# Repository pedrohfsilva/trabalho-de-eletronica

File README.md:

# Fonte de Tensão ajustável(3v - 12v)

Buscamos diagramar e construir uma fonte com capacidade para até 100mA de corrente e uma tensão ajustável dada uma fonte inicial de 127V.

## Transformador

O Transformador é necessário para ajustar a tensão alternada residencial com tensão maxima de 179.6V e frequência de 60Hz para uma tensão que o aparelho possa receber.

A tensão eficaz é o equivalente contínuo de uma fonte alternada e seu cálculo é dado por:  

$V{ef}=\frac{V{max}}{\sqrt{2}}$

$V{ef}=\frac{179.6}{\sqrt{2}}$

$V{ef}\approx127$

A razão entre o número de voltas na espira primária e secundária é diretamente proporcional a razão entre a voltagem primária e secundária 

Logo, a equação se dá por:

$\frac{V_1}{V_2}=\frac{N_1}{N_2}$

Aplicando:

$\frac{179.6}{24.6}=\frac{N_1}{N_2}$

## Diodos / Ponte de diodos

Sem diodos e com uma transformador $\frac{N_1}{N_2}=10$, a tensao em uma resistência, varia conforme o seguinte gráfico (apresentando tensões negativas, o que não é desejado)

Com uma retificador de meia onda, ou seja, apenas um diodo, a tensão em uma resistencia varia da seguinte maneira

Assim, será necessária uma ponte de diodos para retificar a corrente (manter o sentido da corrente após o transformador)
Um diodo permite que a corrente passe em apenas um sentido. Uma ponte de diodos associa 4 diodos como mostrado na imagem para que a fonte alternada de tensões positivas e negativas se polarize apenas em tensões positivas.

(note que dois diodos consomem cerca de 1.4v)

Cada diodo de sílicio consome cerca de 0.7V, e como são utilizados dois por vez, um consumo de 1.4V deve ser considerado. 

## Capacitor

Apos retificar a tensão, é necessário evitar que ela chegue a 0. Para isso, utilizaremos um capacitor, que impede a queda de tensão total, mantendo-a mais próxima de uma voltagem constante para a resistência final.

Em eletrônica, capacitância é uma grandeza oposta à voltagem, sendo gerada pelo acúmulo de carga em uma determinada região, sendo que há inexistência de corrente entre uma região e outra. 
Dessa forma, capacitores são dispositivos compostos por duas placas isoladas entre si e próximas, assim ao passar uma corrente por ele (a corrente não passa realmente pela existência de material isolante entre as placas, apenas é gerada pela indução das cargas), um dos lados terá acúmulo de elétrons que gerará uma indução crescente até que as placas atinjam seu limite de carga (no infinito). Quando a tensão da fonte for menor do que a sua interna, a carga acumulada gerará uma corrente no sentido inverso, até que ela seja novamente 0 (o que não chega a acontecer no nosso circuito).
O tempo de carga de um capacitor até que esse chegue a 98%, pode ser aproximado por $t=5\cdot R\cdot C$

Esse agora é o comportamento da tensão, com um capacitor em paralelo no circuito, a tensão ainda varia nesse padrão que se denomina ripple. E o valor do ripple(diferença entre máximo e mínimo) é calculado por ripple = $\frac{V_2-2\cdot D}{2\cdot f\cdot C\cdot R}$

O valor máximo é a tensão após a fonte de diodos, que é 24.6(medido no transformador)-2Diodos, = 23.2V
O valor mínimo é o maximo decrescido do ripple(cerca de 23.6V, considerando um ripple de 4.3%).

Considerando um ripple de 4.3% após a ponte de diodos (equivalente a 1V) e aplicando na fórmula, a capcitância encontrada é de 1mF, que é um valor comercial.
Agora, resta eliminar o ripple.

## Diodo zener

O diodo zener é um componente eletrônico que permite a passagem da corrente em apenas um sentido como um diodo normal, no outro sentido ele consome uma tensão cosntante. Ele é utilizado na fonte como um regulador de tensão, com o objetivo de manter uma corrente contínua. Para este projeto, a sua tensão limite é de 13V, pois, se esse limite não for atingido, ele não se torna condutor e 13V é o valor comercial mais próximo acima de 12,7V(valor do transitor mais o valor máximo fornecido). Além disso, ele opera a uma potência de 500 miliwatts.

## Transistor

O transistor bipolar é um componente que funciona como amplificador de corrente, sendo que a corrente do coletor para a base é cerca de 100 vezes menor do que a corrente da base para o emissor.
Utilizaremos ele para permitir a passagem da corrente estabilizada ao mesmo tempo em que recebe a tensão controlada pelo zener. O transistor consome 0.7V.

## Potenciometro

O potenciometro opera como uma resistência variável para permitir a troca de tensão fornecida. Quando o seu valor é mínimo, a tensão fornecida é a mesma da tensão que o zener permite menos a tensão consumida pelo transistor. Quando a resistência é máxima, a potência entregue é 0V. Para corrigir isso, adicionamos duas resistências de 820 em série após o potênciometro para que a voltagem mínima seja de cerca de 1.2V.
Foi utilizado um potênciometro de 10k.

# Tabela de Preços

|Componente|Preço unitário|Quantidade|Subtotal
|---|---|---|---|
[Led 5mm Verde](https://www.baudaeletronica.com.br/produto/led-difuso-5mm-verde)|R$ 0,27|1|R$ 0,27
[LED Difuso 3mm Vermelho](https://www.baudaeletronica.com.br/produto/led-difuso-3mm-vermelho)|R$ 0,25|3|R$ 0,75
[LED Difuso 5mm Azul](https://www.baudaeletronica.com.br/produto/led-difuso-5mm-azul)|R$ 0,27|1|R$ 0,27
[Resistor 820R 5% (2W)](https://www.baudaeletronica.com.br/produto/resistor-820r-5-2w.html)|R$ 0,42|4|R$ 1,68
[Transistor NPN 2N2222](https://www.baudaeletronica.com.br/produto/transistor-npn-2n2222.html)|R$ 0,55|4|R$ 2,20
[Ponte Retificadora KBPC1010](https://www.baudaeletronica.com.br/produto/ponte-retificadora-kbpc1010.html)|R$ 4,90|2|R$ 9,80
[Capacitor Eletrolítico 1000uF / 25V](https://www.baudaeletronica.com.br/produto/capacitor-eletrolitico-1000uf-25v-105c.html)|R$ 0,95|4|R$ 3,80
[Resistor 82R 5% (2W)](https://www.baudaeletronica.com.br/produto/resistor-82r-5-2w.html)|R$ 0,42|3|R$ 1,26
[Potenciômetro Linear de 10K (10000Ω)](https://www.baudaeletronica.com.br/produto/potenciometro-linear-de-10k-10000.html)|R$ 2,70|1|R$ 2,70
[Diodo Zener BZX55C (13V / 0.5W)](https://www.baudaeletronica.com.br/produto/diodo-zener-bzx55c-13v-05w.html)|R$ 0,09|5|R$ 0,45
[Resistor 5K1 5% (2W)](https://www.baudaeletronica.com.br/produto/resistor-5k1-5-2w.html)|R$ 0,42|3|R$ 1,26
[Protoboard 170 Pontos Azul](https://www.baudaeletronica.com.br/produto/protoboard-170-pontos-azul.html)|R$ 4,75|2|R$ 9,50
[Resistor 3K 5% (1/4W)](https://www.baudaeletronica.com.br/produto/resistor-3k-5-14w.html)|R$ 0,06|4|R$ 0,24
Frete|||R$ 18,16
TOTAL:|||R$ 52,34

# Circuito do Falstad

## Link para o circuito
[https://tinyurl.com/24aza57k](https://tinyurl.com/2dmqjkqc)

# Esquemático da PCB (EAGLE)

# PCB (EAGLE)

# Imagens - Projeto

# Vídeo - Projeto
https://youtu.be/xrW4_Q9_DJc

## Alunos

Bruno Figueiredo Lima - 14562383

Gabriel Antunes Afonso de Araujo - 14571077

Lázaro Pereira Vinaud Neto - 14675396

Pedro Henrique Ferreira Silva - 14677526

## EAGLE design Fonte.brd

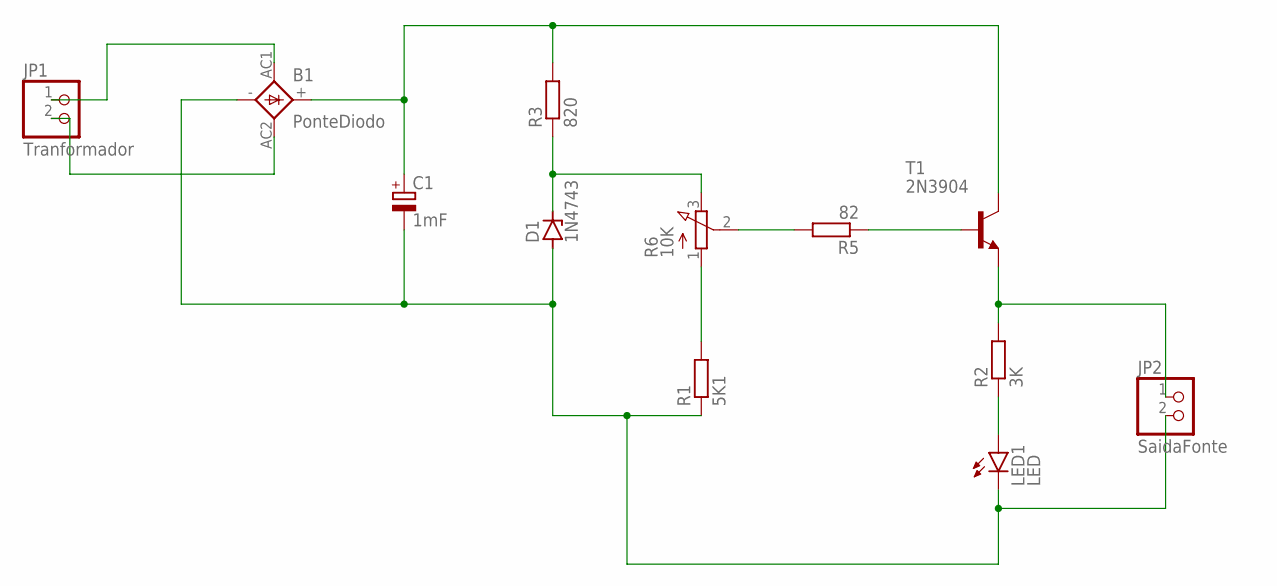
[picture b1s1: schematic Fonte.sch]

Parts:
B1: PonteDiodo; 1KAB
C1: 1mF; E5-10,5
D1: 1N4743; DO41Z10
JP1: Tranformador; 1X02
JP2: SaidaFonte; 1X02
LED1: LED; LED5MM
R1: 5K1; 0204/7
R2: 3K; 0204/7
R3: 820; 0204/7
R5: 82; 0204/7
R6: 10K; 3RP/1610N
T1: 2N3904; TO92

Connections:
unnamed: B1.AC1, JP1.1
unnamed: B1.AC2, JP1.2
unnamed: B1.+, C1.+, R3.2, T1.1 (C)
unnamed: B1.-, C1.-, D1.A, JP2.2, LED1.K (C), R1.1
unnamed: D1.C, R3.1, R6.3 (E)
unnamed: R1.2, R6.1 (A)
unnamed: R5.2, R6.2 (S)
unnamed: R5.1, T1.2 (B)
unnamed: JP2.1, R2.2, T1.3 (E)
unnamed: LED1.A, R2.1

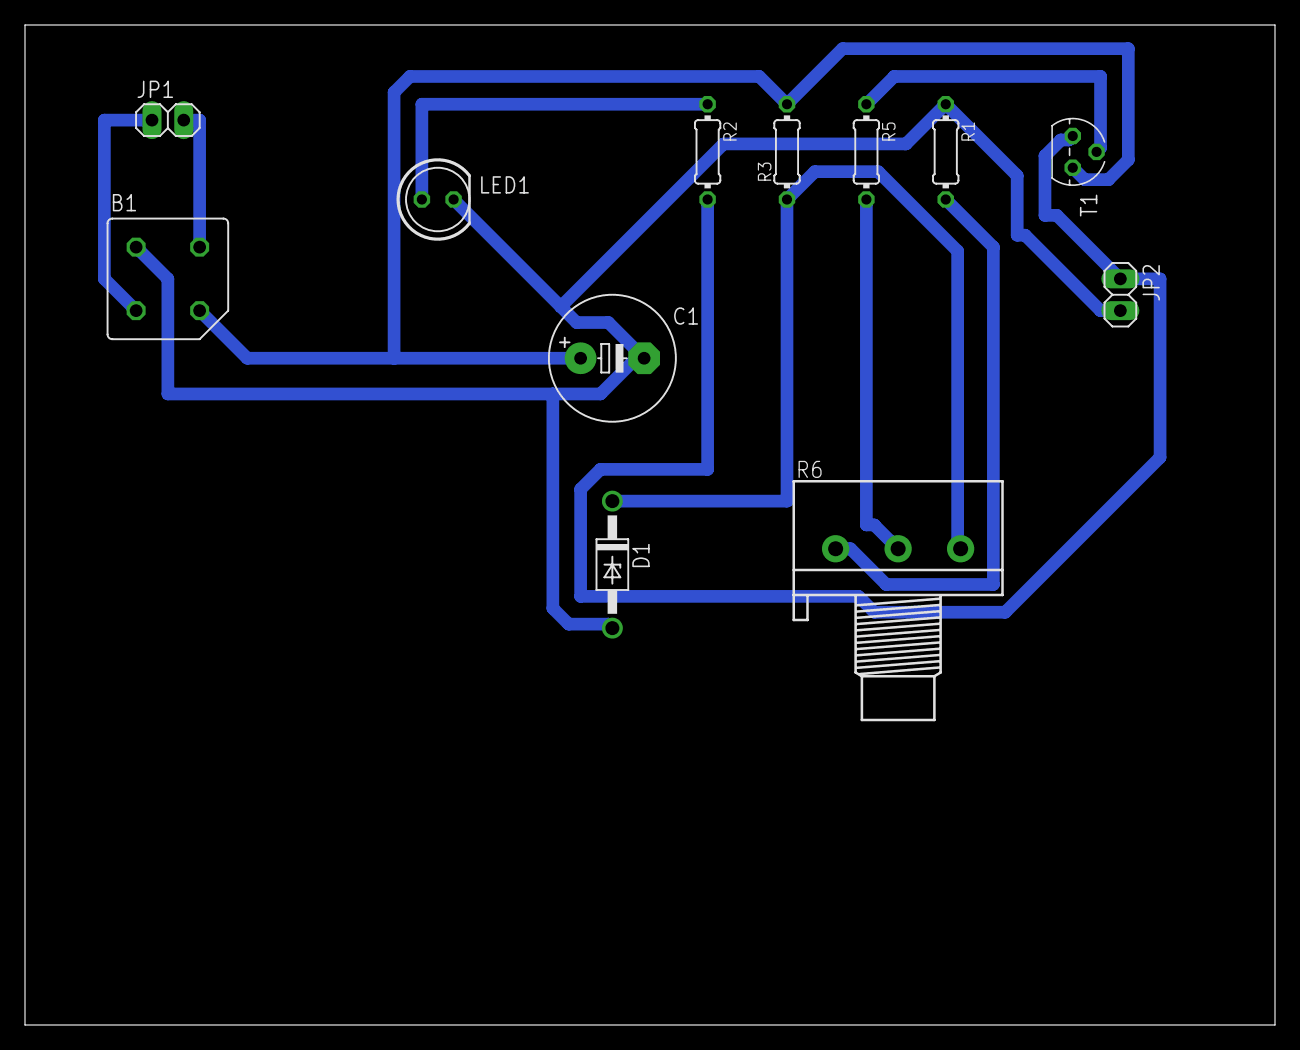
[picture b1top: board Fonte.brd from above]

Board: 2 copper layers, 100.0 x 80.0 mm, 12 parts (0 on the bottom side), 10 nets.

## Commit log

2023-06-22 adicionei pasta com as imagens
